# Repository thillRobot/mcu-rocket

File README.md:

# mcu-rocket
Data Acquisition and Control of a Model Rocket with an MCU based Flight Computer 

Tristan Hill - 2021 - 2025                             

## Overview
This project contains MCU programs and other utilities related to data acquisition and control of a model rocket. The rocket payload contains an on-board flight computer consisting of a micro-controller and sensor package for collecting flight data and environmental conditions during the launch of a model rocket. 

## Astract (GSET 2025)
Space travel is an exciting and important cross discipline engineering application essential for communication, defense, and exploration. Rockets are primarily used for deploying vehicles from earth, and the prediction and measurement of a rocket apogee, or maximum distance from earth, is critical for mission success. Participants will engage in an exciting engineering project including the design, fabrication, and launch of a custom model rocket with an on-board sensor suite and data acquisition payload for monitoring flight performance. The primary goals of the project are designing a rocket capable of successful launch with recovery and predicting and measuring the rocket apogee during flight. Engineering activities include 3D computer aided design (CAD), additive manufacturing and 3D printing, analytical and numerical analysis, computer programming with embedded systems, and empirical testing. Students will be exposed to and learn the basics of Solidworks for CAD, FDM 3D printing, Arduino MCUs and C++ programming, and rocket modeling and analysis.
  
## Mission Information

Note: This is the master README that covers all hardware and missions. The missions are MCU and rocket specific so choose the branch appropriate to the MCU in use for specific code and mission data.

## Intended Schedule, GSET 2025
  - [Week 1](gset_2025/week1): Rocketry, CAD, and 3D printing
    - Monday 6/09 
      - Project introduction and basics of rocketry discussion
      - Visit computer lab, Introduction to CAD with Solidworks, Draw Basic Shapes
      - Preliminary brainstorm rocket design, review previous designs 
      - Discuss Fabrication, Intro to 3D printing

    - Tuesday 6/10
      - Fluid Dynamics Lession, Mach number and Nozzles 
      - Brainstorm, Hand sketch prelimary designs, Discsuss printabilty
      - Visit Computer Lab, Draw Nose Cone, Draw Tail
      - Begin Solidworks install on personal computer if desired    

    - Thursday 6/12 
      - Physics Review: Newton's Laws, Forces, Moments, Inertia, Momentum, Impulse  
      - Rocket Dynamics, Apogee Prediction Discussion, Center of Mass Calculation 
      - Rocket Flight Simulations
      - Solidworks Assembly Demonstration
      - Introduce Flight Computer and Sensor Package, find or model pcbs
      - Visit Computer Lab, Update Designs, include flight computer and sensor package

    - Friday 6/13 
      - Visit Computer Lab, Complete Rocket Designs
      - Final Design Review, Check for Manufacturability 
                  
  - [Week 2](gset_2025/week2): Fabrication, Assembly, and Programming
    - Monday 6/16  
      - Show Flight Computer Circuit Diagram, discuss power 
      - Complete Rocket Designs
      - Group Design Review, Check for Manufacturabilty and Flight
      - Begin Printing Parts

    - Tuesday 6/17 
      - Begin Rocket Assembly
      - Continue Printing Parts, re-print if needed
      - Dynamic analysis and simulation 

    - Wednesday 6/18 
      - Intro to C++ for Arduino
      - Program and Test Sensor Payload
      - Contiue Rocket Assembly

    - Friday 6/20 
      - Continue Programming and Testing
      - Finish Rocket Assembly

  - [Week 3](gset_2025/week3): Launch and Presentation
    - Monday 6/23 - Launch Day 1, Finish Programming Sensor Payload
    - Tuesday 6/24 - Launch Day 2, Review Collected Data
    - Wednesday 6/25 - Launch Day 3, Create Presentation 
    - Friday 6/27 - Final Presentation

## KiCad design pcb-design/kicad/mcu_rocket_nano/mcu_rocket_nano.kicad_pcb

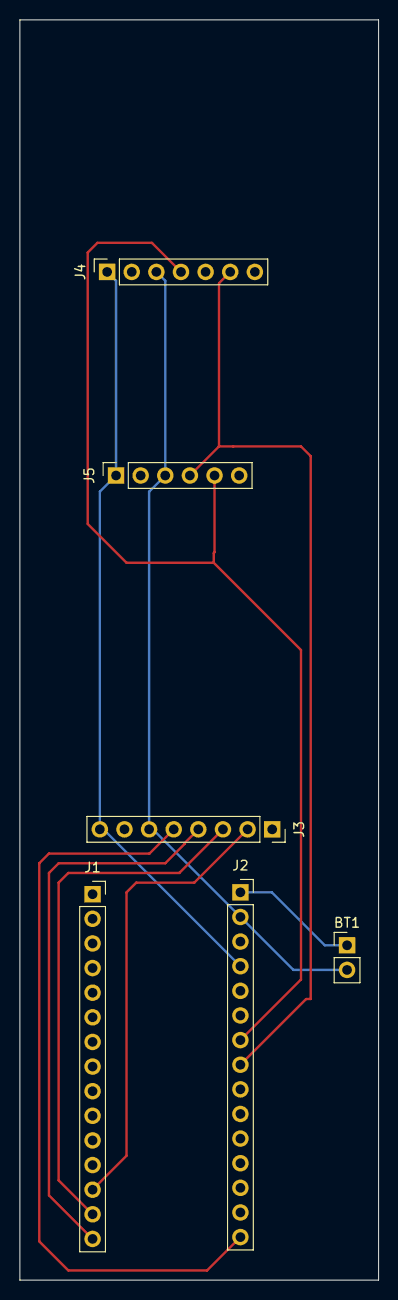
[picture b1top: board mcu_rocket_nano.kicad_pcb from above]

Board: 2 copper layers, 37.0 x 130.0 mm, 6 parts (0 on the bottom side), 9 nets.

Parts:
BT1: Battery_Cell; PinHeader_1x02_P2.54mm_Vertical
J1, J2: Conn_01x15_Socket; PinSocket_1x15_P2.54mm_Vertical
J3: SD Reader; PinSocket_1x08_P2.54mm_Vertical
J4: DPS310; PinSocket_1x07_P2.54mm_Vertical
J5: BNO055; PinSocket_1x06_P2.54mm_Vertical

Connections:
+5V: J2.4 (5V), J3.8 (5V), J4.1 (VIN), J5.1 (VIN)
GND: BT1.2 (-), J2.2 (GND), J3.6 (GND), J4.3 (GND), J5.3 (GND)
unnamed: J1.13 (D10), J3.2 (CS)
unnamed: J1.14 (D11), J3.3 (DI)
unnamed: J1.15 (D12), J3.4 (DO)
unnamed: J2.8 (A4), J4.6 (SDI), J5.4 (SDA)
unnamed: J2.7 (A5), J4.4 (SCK), J5.5 (SCL)
unnamed: J2.15 (D13), J3.5 (CLK)
VCC: BT1.1 (+), J2.1 (VIN)

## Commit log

2021-06-06 added files from /mcu/sd/data_logger_mkr
2021-06-06 added branch nano-master
2021-06-06 added README.md
2021-06-06 split into branches for each MCU
2021-06-06 deleted license in master accidentally
2021-06-06 re-added license file to master
2021-06-06 fixed README for branch mkr-master
2021-06-06 fixed README for branch nano-master
2021-06-06 fixing READMEs for branches
2021-06-06 branch nano-master tested, working, code size maxed
2021-06-06 tested branch mkr-master, working as expected
2021-06-24 cleaning up
2021-06-25 added launch 06/24/2021 data and python/parse.py
2021-06-25 added screenshots to show launch_06_24_2021
2021-06-25 added rocket-design with PNG images and rocket_design_tables.xlsx
2021-06-26 Improved repository project description
2021-06-26 trying to organize READMEs for different missions
2021-06-26 removed mission code from master, see branches
2021-06-26 added flight log and data for Flight 0
2021-06-26 added link to launch videos
2021-06-26 added rocket-design.md
2021-06-26 added rocket-design/README.md
2021-06-26 adding relative links to images
2021-06-27 added design story for Nano-Rocket
2021-06-27 added fusion images to nano-rocket design story
2021-06-28 moved images to rocket-design/png-images
2021-06-28 replaced Strings and c strings
2021-06-29 replaced sprintf() with snprintf() to prevent c string overflow
2021-06-29 improved file/serial buffer handling
2021-06-30 updated links to /rocket-design/png-images
2021-06-30 added nosecone_construction images
2021-07-01 replaced Strings with char arrays
2021-07-01 fixed upper case png file extensions
2021-07-01 fixed links to png images and uppercase extensions
2021-07-01 added interrupt based timestamps to datalog
2021-07-01 changed printData to printSensors
2021-07-01 adding DPS310, i2c error
2021-07-03 optimized data-logger for size and memory
2021-07-03 nano data-logger BNO055 and DPS310 working
2021-07-11 cleaning up docs
2025-06-09 added schedule to README
2025-06-09 adding week1 content
2025-06-09 adding link to guide
2025-06-09 adding day1 outline
2025-06-10 updating intro to rocketry
2025-06-10 added rocket_design.md
2025-06-10 adding week1 README
2025-06-10 updating week1 README
2025-06-10 updateing schedule in README
2025-06-12 added flight_computer.md
2025-06-12 moved flight computer to week2
2025-06-12 added week2 README
2025-06-12 adding links to TOC
2025-06-12 added week3, cleaning up slowly
2025-06-12 adding physics review
2025-06-12 updated TOC
2025-06-12 updating physics review
2025-06-12 updated physics review again
2025-06-16 updating schedule in README
2025-06-16 updating schedule
2025-06-25 added gset 2025 launch data
2025-06-27 updating parse.py for 2025 launch data
2025-06-27 updating parse.py, testing plots
2025-06-27 added altitude to parse.py
2025-06-27 updated parse.py for 2025 launchdata
2025-06-27 updated parse.py
2025-06-27 parsing launch-data gset 2025
2026-05-27 added kicad files
